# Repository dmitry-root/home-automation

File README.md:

# Домашняя автоматизация

В этом репозитории собраны исходные коды прошивок, драйверов, утилит и серверных
приложений, используемых для автоматизации у меня дома. Подозреваю, что этот код
никому, кроме меня, не интересен. Но на всякий случай сообщаю, что код выложен
под лицензией MIT и доступен для свободного использования и модификации при условии
сохранения текста лицензии в неизменном виде.

Если Вы случайно наткнулись на этот проект и он Вас заинтересовал, можете связаться
со мной по электронной почте. Адрес указан в тексте лицензии.

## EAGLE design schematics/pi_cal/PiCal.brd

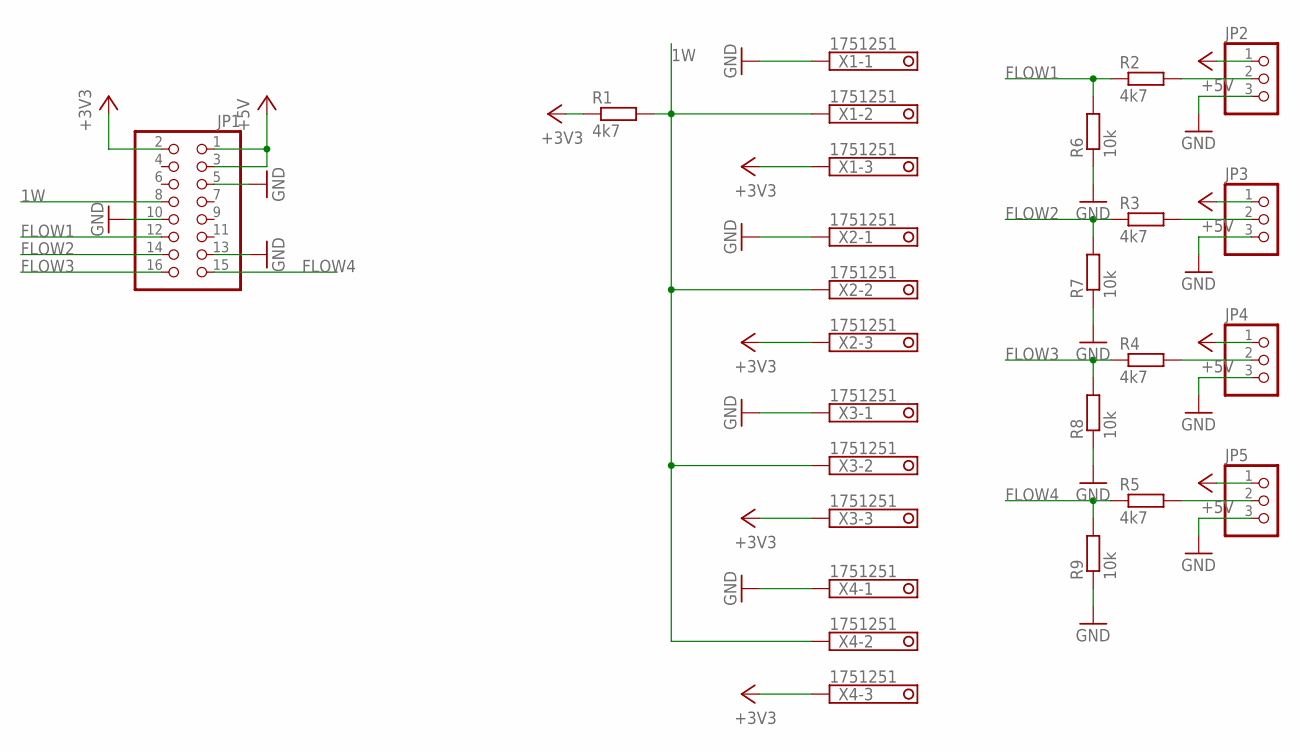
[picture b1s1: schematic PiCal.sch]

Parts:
JP1: PINHD-2X8; 2X08
JP2, JP3, JP4, JP5: PINHD-1X3; 1X03
R1, R2, R3, R4, R5: 4k7; M0805
R6, R7, R8, R9: 10k; M0805
X1, X2, X3, X4: 1751251

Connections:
1W: JP1.8, R1.2, X1.2, X2.2, X3.2, X4.2
+3V3: JP1.2, R1.1, X1.3, X2.3, X3.3, X4.3
+5V: JP1.1, JP1.3, JP2.1, JP3.1, JP4.1, JP5.1
FLOW1: JP1.12, R2.1, R6.2
FLOW2: JP1.14, R3.1, R7.2
FLOW3: JP1.16, R4.1, R8.2
FLOW4: JP1.15, R5.1, R9.2
GND: JP1.5, JP1.10, JP1.13, JP2.3, JP3.3, JP4.3, JP5.3, R6.1, R7.1, R8.1, R9.1, X1.1, X2.1, X3.1, X4.1
unnamed: JP2.2, R2.2
unnamed: JP3.2, R3.2
unnamed: JP4.2, R4.2
unnamed: JP5.2, R5.2

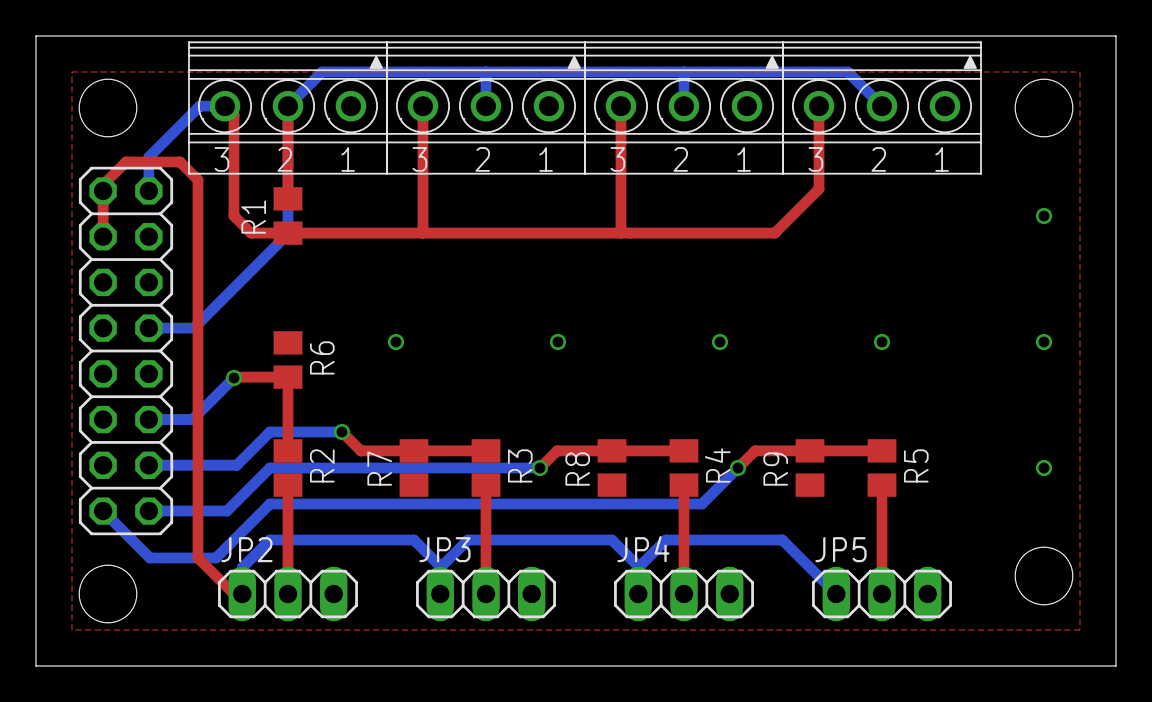
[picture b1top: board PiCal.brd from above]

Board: 4 copper layers, 60.0 x 35.0 mm, 18 parts (0 on the bottom side), 12 nets.

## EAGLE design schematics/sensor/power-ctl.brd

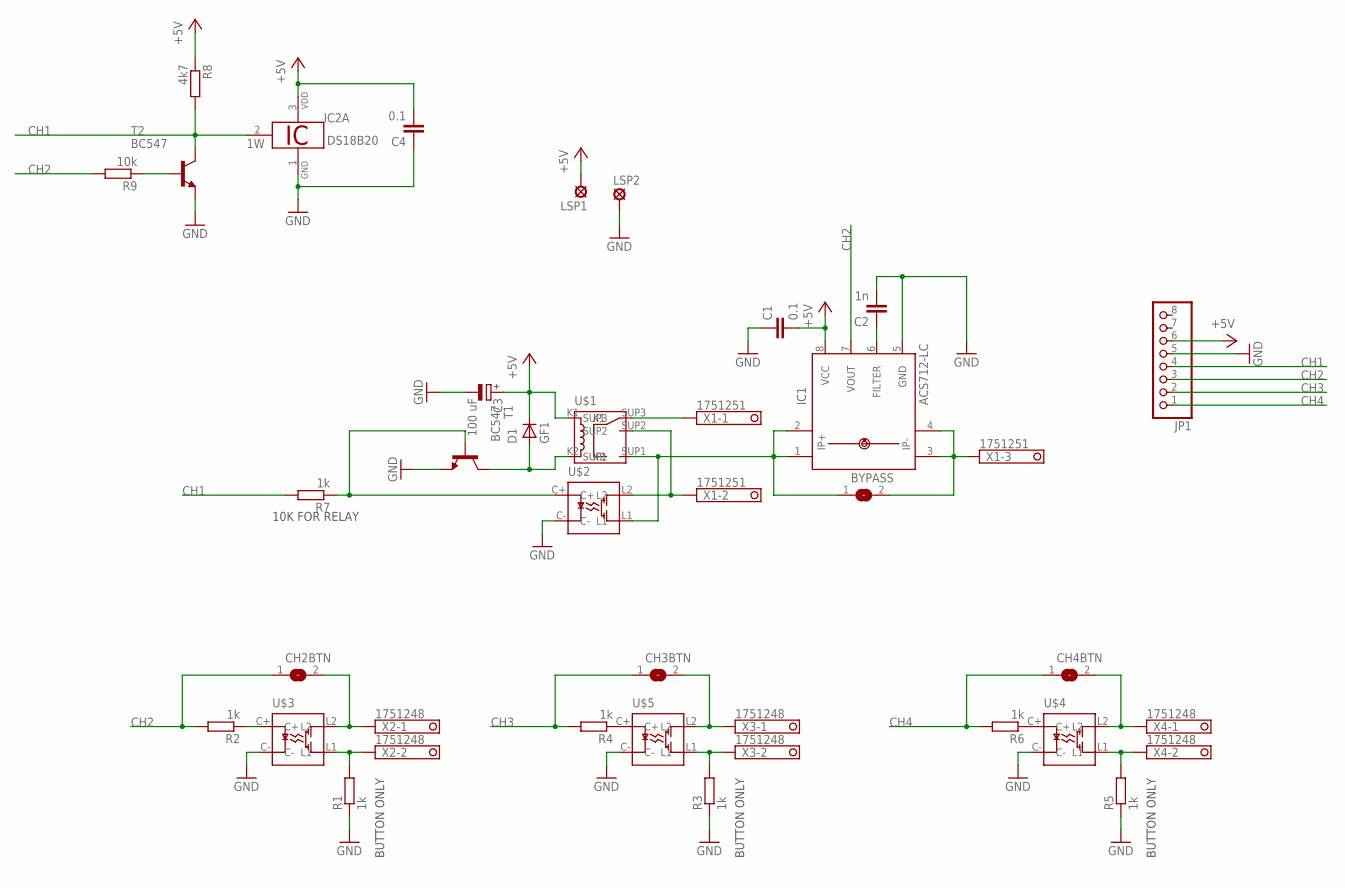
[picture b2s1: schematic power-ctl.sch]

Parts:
BYPASS: SJ
C1, C4: 0.1; C0805
C2: 1n; C0805
C3: 100 uF; E2-4
CH2BTN, CH3BTN, CH4BTN: SJ
D1: GF1; SMA-DO214AC
IC1: ACS712-LC; SOIC8
IC2: DS18B20; TO92-
JP1: PINHD-1X8/90; 1X08/90
LSP1, LSP2: LSP10
R1, R2, R3, R4, R5, R6, R7: 1k; M0805
R8: 4k7; M0805
R9: 10k; M0805
T1, T2: BC547; TO92
U$1: TRV-5VDC-SC-CD
U$2, U$3, U$4, U$5: CPC1030N; SOP4
X1: 1751251
X2, X3, X4: 1751248

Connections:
+5V: C1.2, C3.+, C4.2, D1.K (C), IC1.8 (VCC), IC2.3 (VDD), JP1.6, LSP1.MP, R8.1, U$1.K1
CH1: IC2.2 (1W), JP1.4, R7.2, R8.2, T2.3 (C)
CH2: CH2BTN.1, IC1.7 (VOUT), JP1.3, R2.2, R9.2
CH3: CH3BTN.1, JP1.2, R4.2
CH4: CH4BTN.1, JP1.1, R6.2
GND: C1.1, C2.2, C3.-, C4.1, IC1.5 (GND), IC2.1 (GND), JP1.5, LSP2.MP, R1.1, R3.1, R5.1, T1.1 (E), T2.1 (E), U$2.C-, U$3.C-, U$4.C-, U$5.C-
unnamed: BYPASS.2, IC1.3 (IP-), IC1.4 (IP-1), X1.3
unnamed: BYPASS.1, IC1.1 (IP+), IC1.2 (IP+1), U$1.SUP1, U$2.L1
unnamed: R1.2, U$3.L1, X2.2
unnamed: CH2BTN.2, U$3.L2, X2.1
unnamed: R2.1, U$3.C+
unnamed: R3.2, U$5.L1, X3.2
unnamed: CH3BTN.2, U$5.L2, X3.1
unnamed: CH4BTN.2, U$4.L2, X4.1
unnamed: R5.2, U$4.L1, X4.2
unnamed: R4.1, U$5.C+
unnamed: R6.1, U$4.C+
unnamed: C2.1, IC1.6 (FILTER)
unnamed: D1.A, T1.3 (C), U$1.K2
unnamed: U$1.SUP2, U$2.L2, X1.2
unnamed: R7.1, T1.2 (B), U$2.C+
unnamed: U$1.SUP3, X1.1
unnamed: R9.1, T2.2 (B)

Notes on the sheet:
BUTTON ONLY
10K FOR RELAY

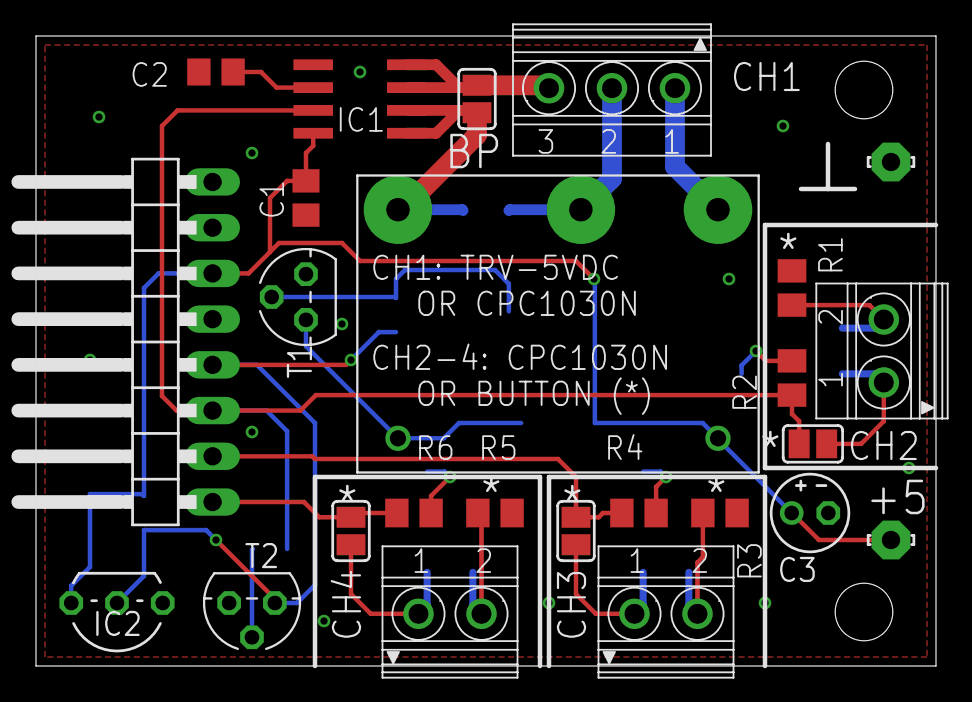
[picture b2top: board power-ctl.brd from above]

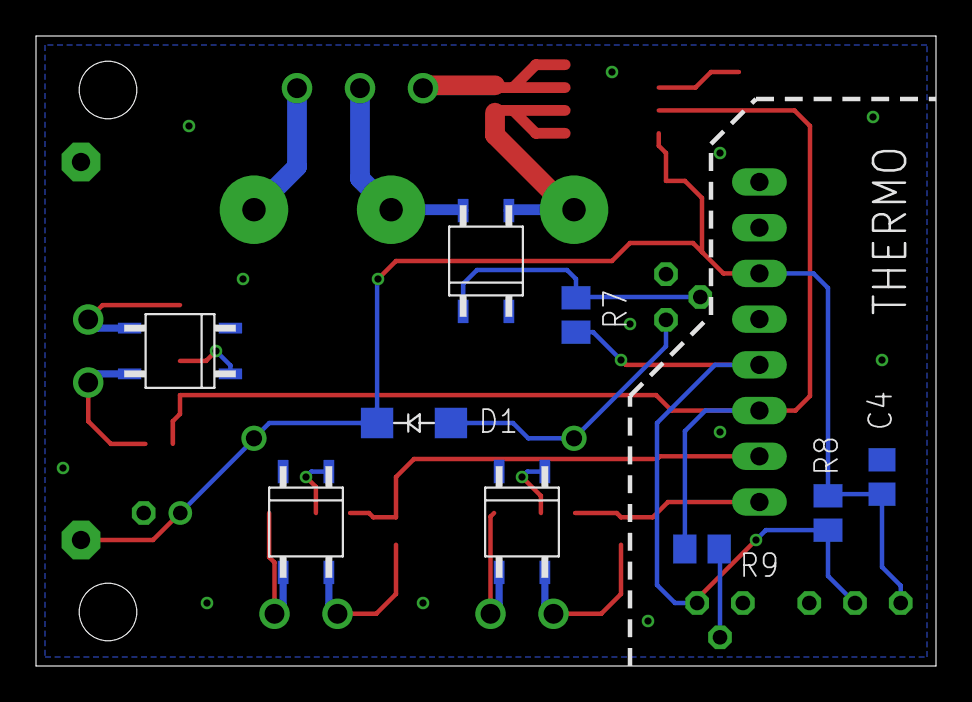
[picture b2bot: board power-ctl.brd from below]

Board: 2 copper layers, 50.0 x 35.0 mm, 34 parts (9 on the bottom side), 23 nets.

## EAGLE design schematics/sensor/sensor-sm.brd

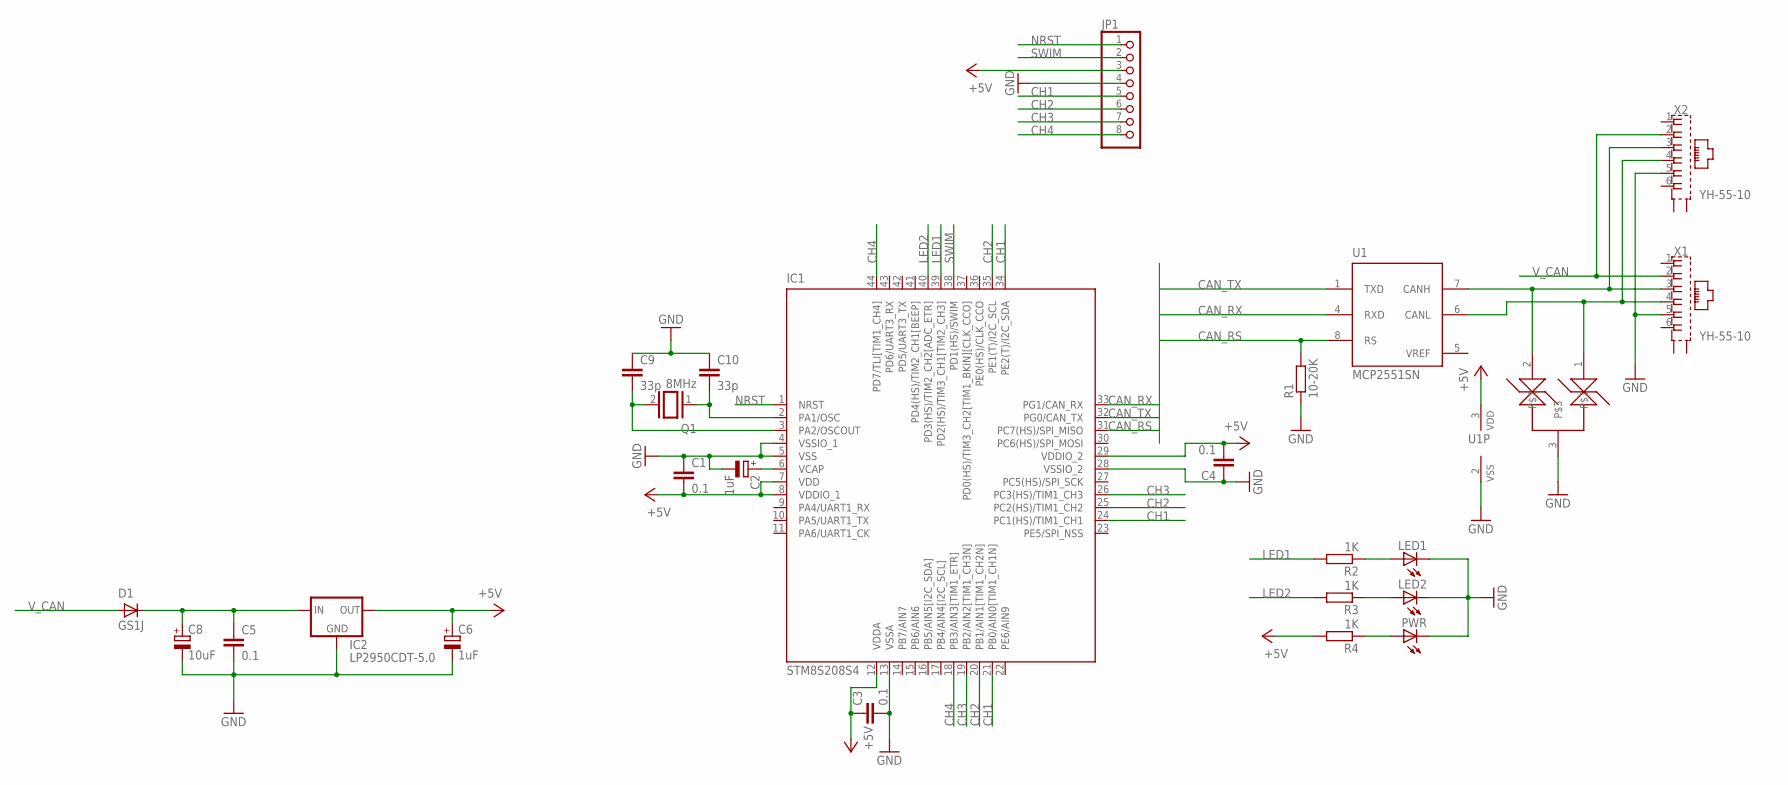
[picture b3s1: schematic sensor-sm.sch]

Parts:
C1, C3, C4, C5: 0.1; C0805K
C2, C6: 1uF; E2-4
C8: 10uF; E2-4
C9, C10: 33p; C0805K
D1: GS1J; SMA-DO214AC
IC1: STM8S208S4; LQFP44-10X10
IC2: LP2950CDT-5.0; DPACK
JP1: PINHD-1X8/90; 1X08/90
LED1, LED2: LEDSML1206; SML1206
NUP2105L: NUP2105L; SOT23
PWR: LEDSML1206; SML1206
Q1: 8MHz; QS
R1: 10-20K; R0805
R2, R3, R4: 1K; R0805
U1: MCP2551SN; SO-08
X1, X2: YH-55-10

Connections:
+5V: C1.2, C3.1, C4.2, C6.+, IC1.7 (VDD), IC1.8 (VDDIO_1), IC1.12 (VDDA), IC1.29 (VDDIO_2), IC2.3 (OUT), JP1.3, R4.2, U1.3 (VDD)
CAN_RS: IC1.31 (PC7(HS)/SPI_MISO), R1.2, U1.8 (RS)
CAN_RX: IC1.33 (PG1/CAN_RX), U1.4 (RXD)
CAN_TX: IC1.32 (PG0/CAN_TX), U1.1 (TXD)
CH1: IC1.21 (PB0/AIN0[TIM1_CH1N]), IC1.24 (PC1(HS)/TIM1_CH1), IC1.34 (PE2(T)/I2C_SDA), JP1.5
CH2: IC1.20 (PB1/AIN1[TIM1_CH2N]), IC1.25 (PC2(HS)/TIM1_CH2), IC1.35 (PE1(T)/I2C_SCL), JP1.6
CH3: IC1.19 (PB2/AIN2[TIM1_CH3N]), IC1.26 (PC3(HS)/TIM1_CH3), JP1.7
CH4: IC1.18 (PB3/AIN3[TIM1_ETR]), IC1.44 (PD7/TLI[TIM1_CH4]), JP1.8
GND: C1.1, C2.-, C3.2, C4.1, C5.2, C6.-, C8.-, C9.1, C10.1, IC1.4 (VSSIO_1), IC1.5 (VSS), IC1.13 (VSSA), IC1.28 (VSSIO_2), IC2.4 (GND), JP1.4, LED1.C, LED2.C, NUP2105L.3, PWR.C, R1.1, U1.2 (VSS), X1.5, X2.5
LED1: IC1.39 (PD2(HS)/TIM3_CH1[TIM2_CH3]), R2.2
LED2: IC1.40 (PD3(HS)/TIM2_CH2[ADC_ETR]), R3.2
unnamed: C2.+, IC1.6 (VCAP)
unnamed: C10.2, IC1.2 (PA1/OSC), Q1.1
unnamed: NUP2105L.1, U1.6 (CANL), X1.4, X2.4
unnamed: C9.2, IC1.3 (PA2/OSCOUT), Q1.2
unnamed: LED1.A, R2.1
unnamed: LED2.A, R3.1
unnamed: PWR.A, R4.1
unnamed: NUP2105L.2, U1.7 (CANH), X1.3, X2.3
unnamed: C5.1, C8.+, D1.K (C), IC2.1 (IN)
NRST: IC1.1 (NRST), JP1.1
SWIM: IC1.38 (PD1(HS)/SWIM), JP1.2
VREF: U1.5 (VREF)
V_CAN: D1.A, X1.2, X2.2

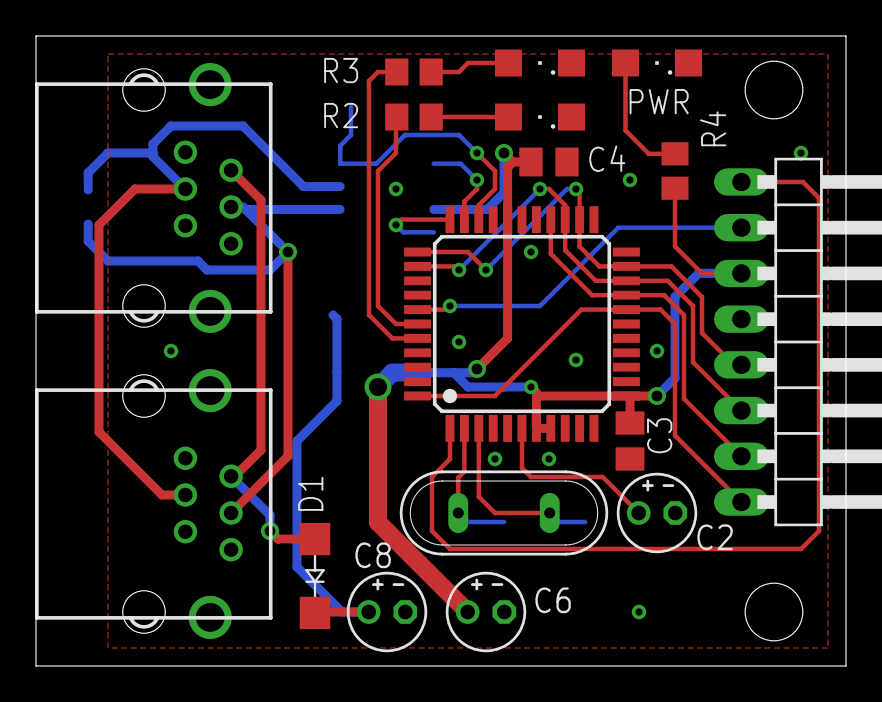
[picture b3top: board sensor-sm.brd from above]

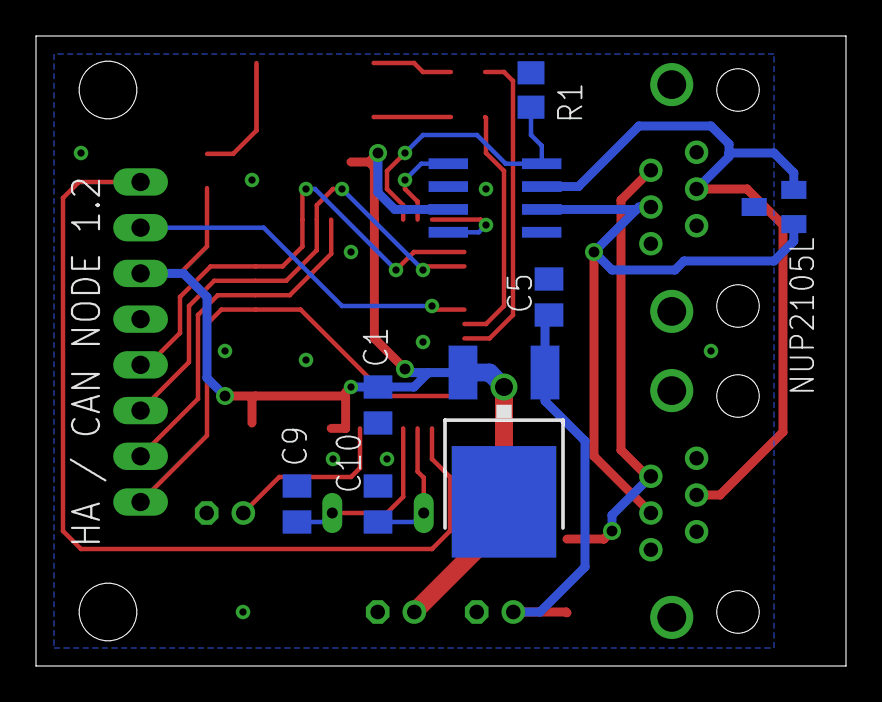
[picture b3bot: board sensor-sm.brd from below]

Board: 2 copper layers, 45.0 x 35.0 mm, 25 parts (8 on the bottom side), 23 nets.

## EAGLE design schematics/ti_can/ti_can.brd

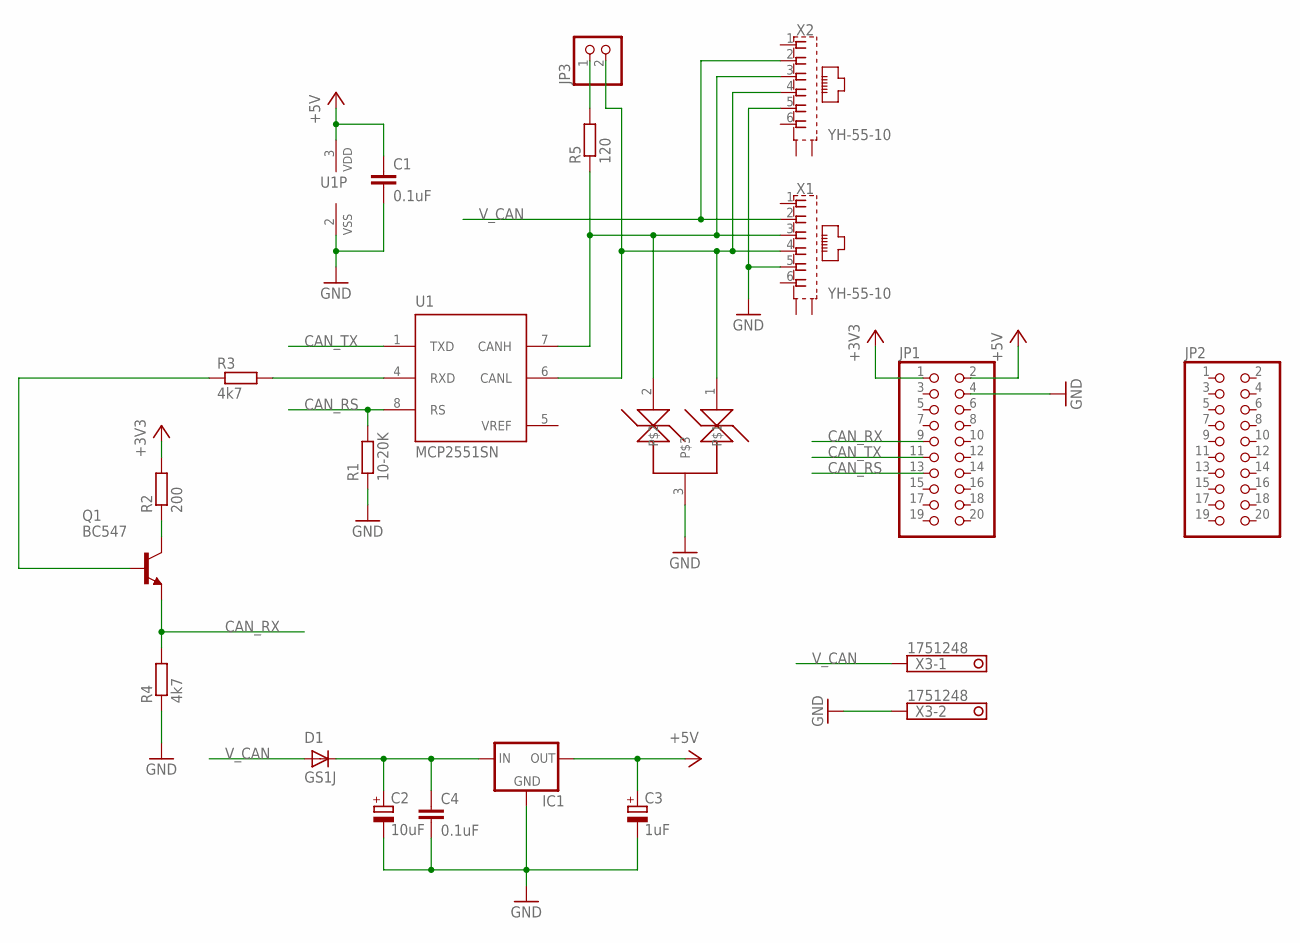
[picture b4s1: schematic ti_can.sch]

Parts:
C1, C4: 0.1uF; C0805
C2: 10uF; E2,5-6E
C3: 1uF; E2,5-6E
D1: GS1J; SMA-DO214AC
IC1: LP2950CDT-5.0; DPACK
JP1, JP2: PINHD-2X10; 2X10
JP3: PINHD-1X2; 1X02
Q1: BC547; TO92
R1: 10-20K; M0805
R2: 200; M0805
R3, R4: 4k7; M0805
R5: 120; 0207/2V
U1: MCP2551SN; SO-08
U$1: NUP2105L; SOT23
X1, X2: YH-55-10
X3: 1751248

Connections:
+3V3: JP1.1, R2.2
+5V: C1.1, C3.+, IC1.3 (OUT), JP1.2, U1.3 (VDD)
CAN_RS: JP1.13, R1.2, U1.8 (RS)
CAN_RX: JP1.9, Q1.1 (E), R4.2
CAN_TX: JP1.11, U1.1 (TXD)
GND: C1.2, C2.-, C3.-, C4.2, IC1.4 (GND), JP1.4, R1.1, R4.1, U1.2 (VSS), U$1.3, X1.5, X2.5, X3.2
unnamed: JP3.2, U1.6 (CANL), U$1.1, X1.4, X2.4
unnamed: Q1.3 (C), R2.1
unnamed: R3.2, U1.4 (RXD)
unnamed: Q1.2 (B), R3.1
unnamed: JP3.1, R5.2
unnamed: C2.+, C4.1, D1.K (C), IC1.1 (IN)
unnamed: R5.1, U1.7 (CANH), U$1.2, X1.3, X2.3
VREF: U1.5 (VREF)
V_CAN: D1.A, X1.2, X2.2, X3.1

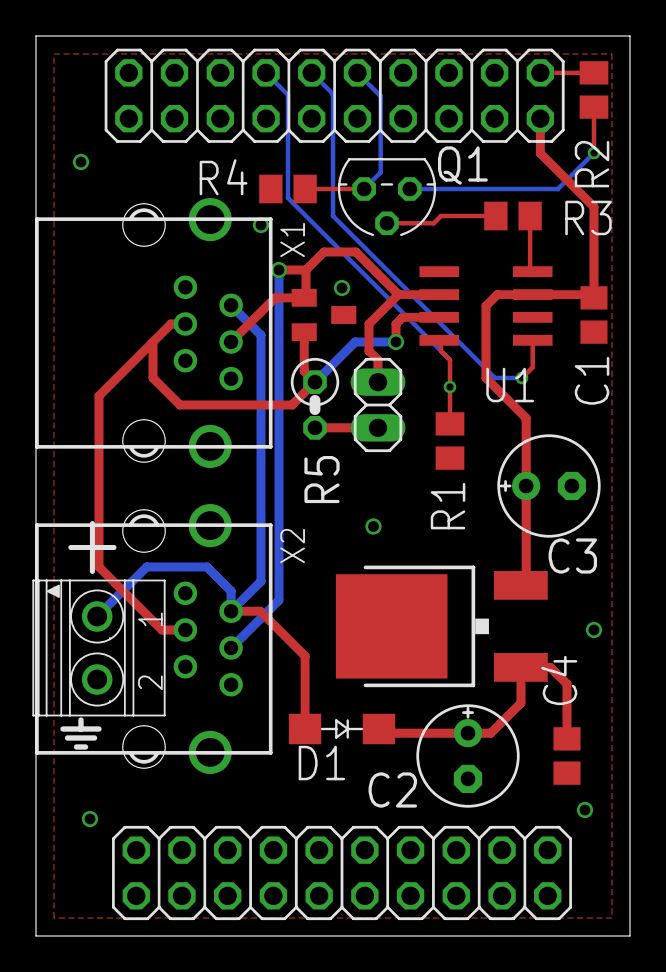
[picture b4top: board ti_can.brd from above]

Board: 2 copper layers, 33.0 x 50.0 mm, 20 parts (0 on the bottom side), 14 nets.

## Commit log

2015-11-06 Update README and license text
2015-11-07 Add build system for TI RTOS projects.
    This commit also adds an empty project for heater automation.
2015-11-07 Add top-level makefiles
2015-11-07 Move output directory one more level up, to the project root.
2015-11-07 Add some helpful classes into include/utils.
2015-11-07 Start work on 1-wire protocol support.
    Add stub class onewire::Session.
2015-11-10 Add one-wire bus software driver.
2015-11-10 Add ds18b20 thermometer support to the 1wire lib.
2015-11-18 Add .bin target for executables
2016-01-08 Add schematics for CAN node
2016-01-08 Debug soft-1-wire (not working yet), add some test code
2016-01-15 Add stm8 build script, standard library (patched for sdcc) and test dummy project
2016-01-18 Add config for shared headers folder
2016-01-27 Exclude depfiles from build on stm8, as sdcpp searches include files in /usr
2016-01-27 Add CAN protocol description and typedefs
2016-01-27 Implement LED access in can_node
2016-01-29 Add some work on CAN Node firmware
2016-01-30 CAN Node: add 100ms clock, implement base protocol, implement main()
2016-03-30 Add latest changes to the home-automation project
2016-03-31 Add some fixes in stm8 code
2016-04-03 More debug
2016-05-02 Implement ds18b20 support on CAN node device
2016-05-25 Add power-ctl board
2016-05-25 Update firmware to support better backward compatibility
2016-05-28 Implement Button module in CAN Node firmware.
2016-06-02 Add analog sensor module
2016-08-10 Implement support for auto-off in switches.
2016-08-12 Add gtest source code
2016-08-12 Add deephome common library and build scripts
2016-08-13 Add service command packet for internal commands that do not affect devices
2016-08-13 Add generic event loop helper
2016-08-13 Add IO async event listener
2016-08-13 Add POSIX signal listener
2016-08-13 Use const-ness to control EventLoop ownership/usage
2016-08-13 Add proto::Connection and SocketConnection classes
2016-08-13 Add SocketServer class
2016-08-14 Add EPIPE error handling
2016-08-14 Add asynchronous write operation in SocketConnection
2016-08-14 Fix error handling in SocketConnection
2016-08-14 Add Timeout handler to EventLoop component
2016-08-14 Add raw arguments support in proto::Message
2016-08-14 Add router::Router class implementation (not tested)
2016-08-14 Add Application class for dhrouter (not tested)
2016-08-16 Add netstub application for testing router. Fix errors found in testing.
2016-08-22 Add DH Router client, implement client::Dispatcher
2016-08-23 Implement request scheduling in Router.
    The each new request is sent only in a specified period of time.
2016-08-23 Implement template-based querying in Dispatcher.
2016-08-25 Use std::optional instead of pointer
2016-09-04 Add Device class to the dhcommon library
2016-09-04 Add CanNode and SwitchChannel classes implementation
2016-09-06 Implement the other channel types in client lib
2016-11-25 Lower CAN frequency to allow longer lines
2016-11-25 Add build script for release
2016-11-25 Add support of DEEPHOME_INSTALL_PREFIX envvar
2016-11-25 Add -d parameter support to dhrouter
2019-02-04 Controller code (outdated)
2019-02-04 Add PiCal board schematics
2019-02-05 Start working on RPI based devices
2019-02-06 Add monitors.py
2019-02-09 Add websensor.py, make it to compile
2019-03-17 Add configs
2019-03-17 +x websensor.py
2019-03-17 Rewrite using RPi.GPIO module
